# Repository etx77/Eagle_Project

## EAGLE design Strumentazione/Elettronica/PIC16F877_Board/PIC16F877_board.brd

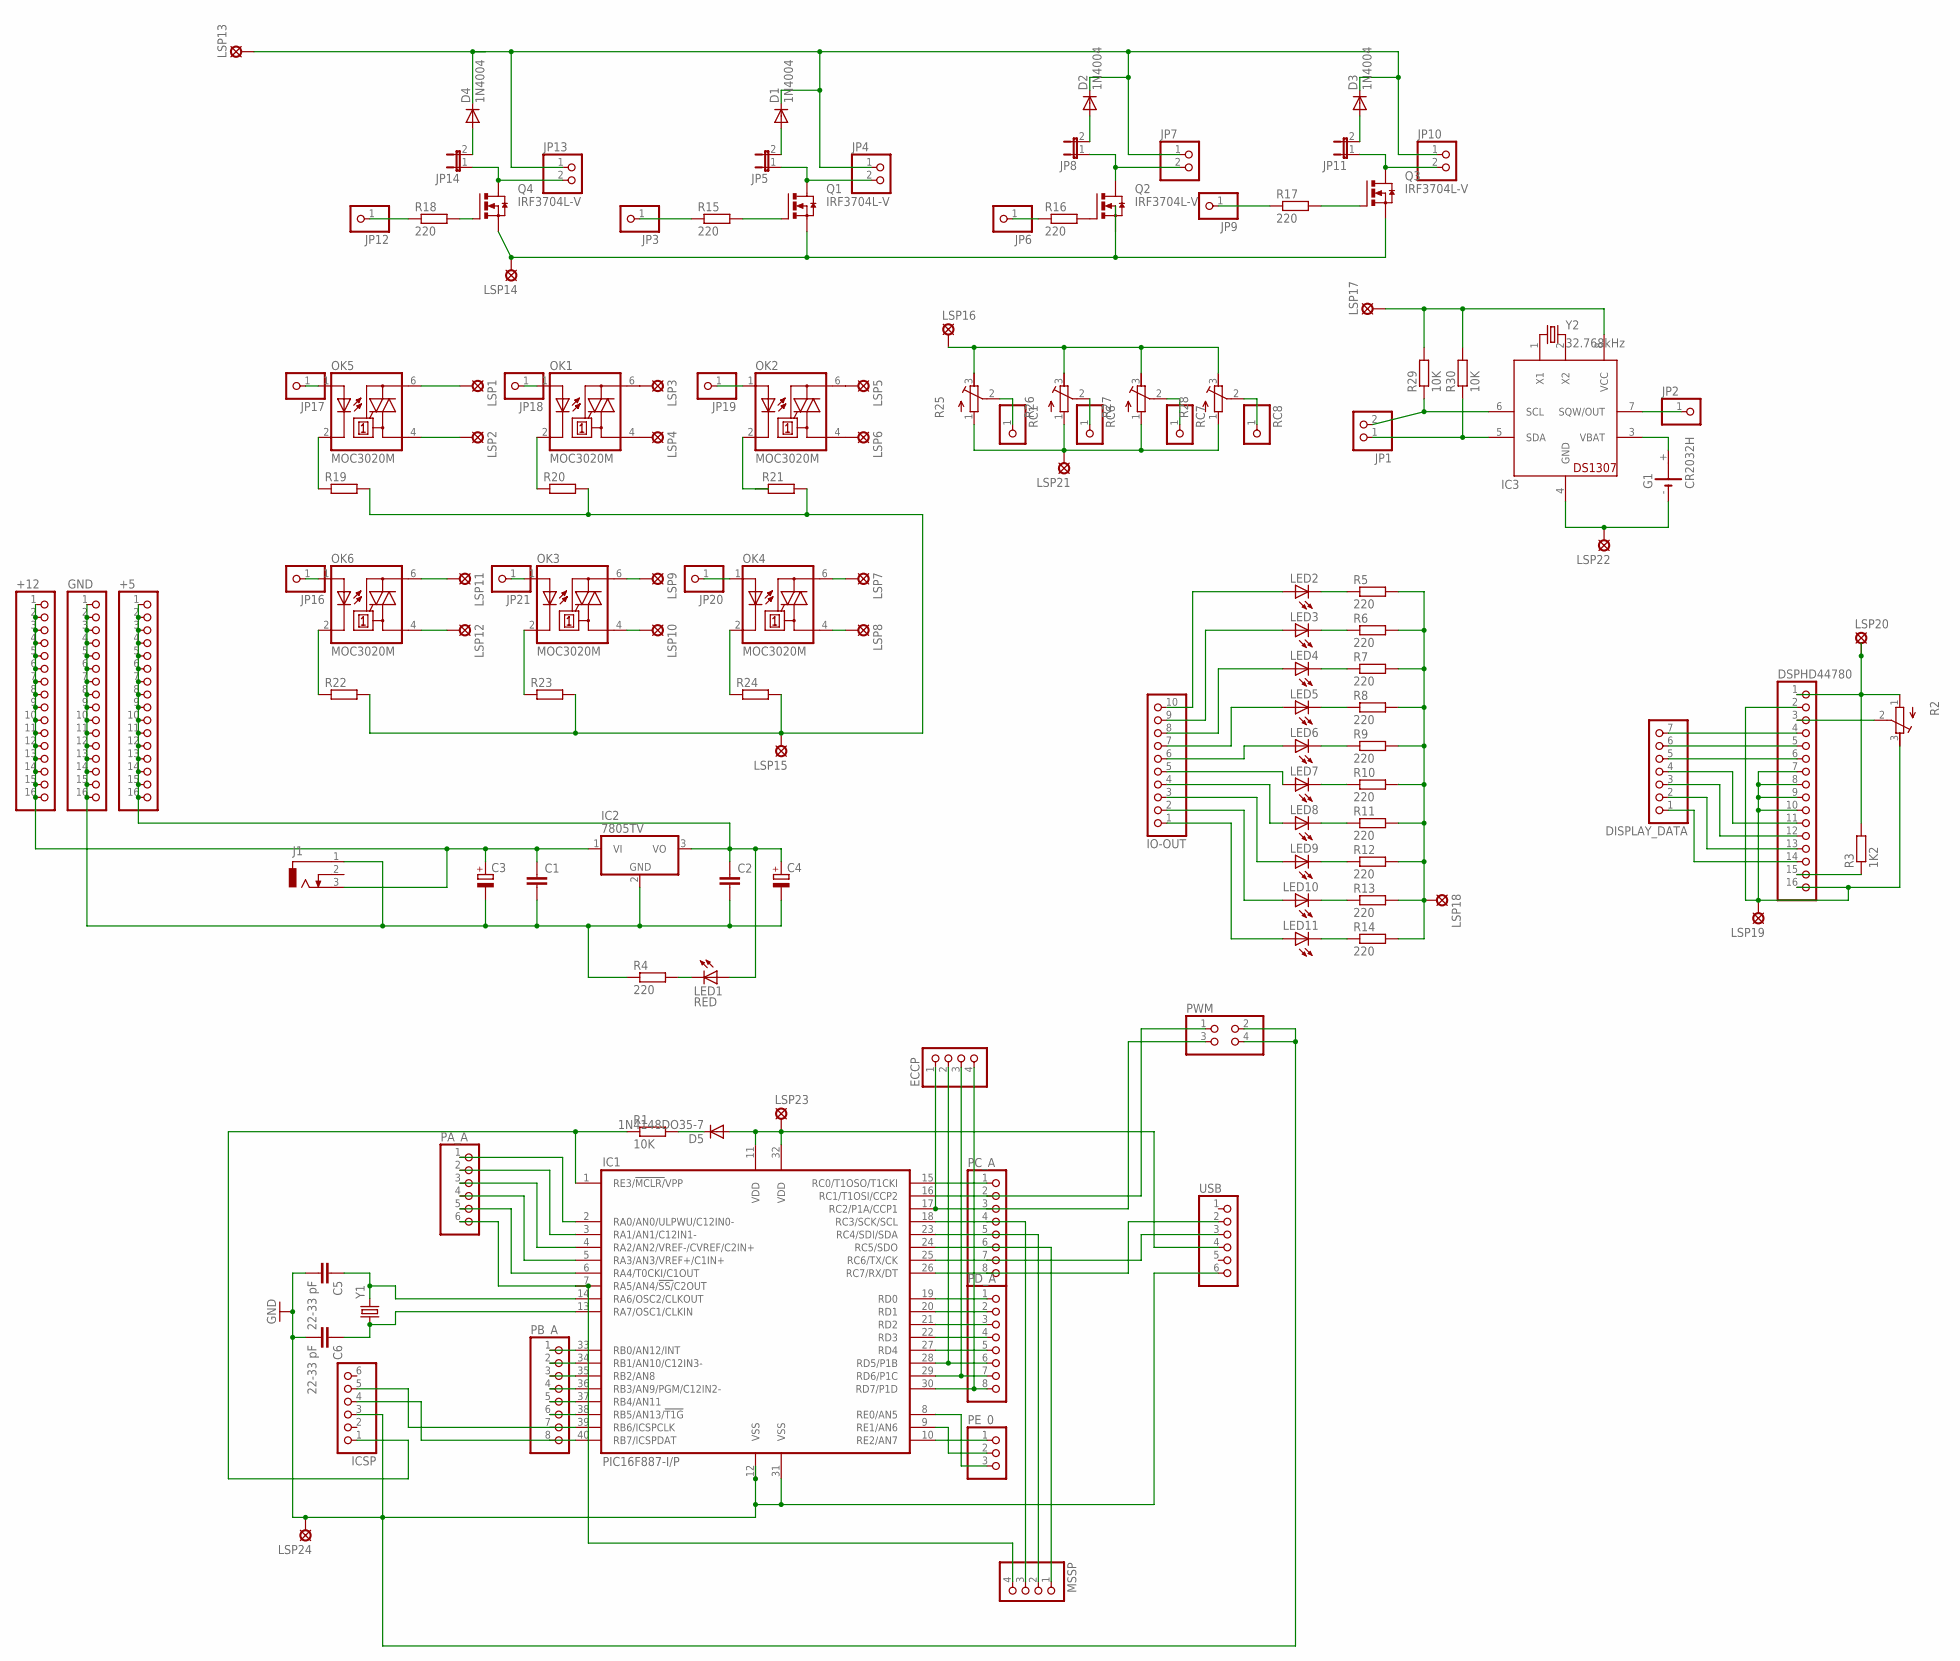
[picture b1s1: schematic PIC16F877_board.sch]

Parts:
+5, +12: PINHD-1X16; 1X16
C1, C2: C-EU050-025X075; C050-025X075
C3, C4: CPOL-EUE2,5-6E; E2,5-6E
C5, C6: 22-33 pF; C025-024X044
D1, D2, D3, D4: 1N4004; DO41-10
D5: 1N4148DO35-7; DO35-7
DISPLAY_DATA: PINHD-1X7; 1X07
DSPHD44780: PINHD-1X16; 1X16
ECCP: PINHD-1X4; 1X04
G1: CR2032H
GND: PINHD-1X16; 1X16
IC1: PIC16F887-I/P; DIL40
IC2: 7805TV; TO220V
IC3: DS1307; DIL08
ICSP: PINHD-1X6; 1X06
IO-OUT: PINHD-1X10; 1X10
J1: DCJ0303
JP1, JP4, JP7, JP10, JP13: PINHD-1X2; 1X02
JP2, JP3, JP6, JP9, JP12, JP16, JP17, JP18, JP19, JP20, JP21: PINHD-1X1; 1X01
JP5, JP8, JP11, JP14: JP1E; JP1
LED1: RED; LED5MM
LED2, LED3, LED4, LED5, LED6, LED7, LED8, LED9, LED10, LED11: LED3MM
LSP1, LSP2, LSP3, LSP4, LSP5, LSP6, LSP7, LSP8, LSP9, LSP10, LSP11, LSP12, LSP13, LSP14, LSP15, LSP16, LSP17, LSP18, LSP19, LSP20, LSP21, LSP22, LSP23, LSP24: LSP10
MSSP: PINHD-1X4; 1X04
OK1, OK2, OK3, OK4, OK5, OK6: MOC3020M; DIL06
PA_A: PINHD-1X6; 1X06
PB_A: PINHD-1X8; 1X08
PC_A: PINHD-1X8; 1X08
PD_A: PINHD-1X8; 1X08
PE_0: PINHD-1X3; 1X03
PWM: PINHD-2X2; 2X02
Q1, Q2, Q3, Q4: IRF3704L-V; TO262-V
R1, R29, R30: 10K; 0207/10
R2, R25, R26, R27, R28: R-TRIMM3339P; RTRIM3339P
R3: 1K2; 0207/10
R4, R5, R6, R7, R8, R9, R10, R11, R12, R13, R14, R15, R16, R17, R18: 220; 0207/10
R19, R20, R21, R22, R23, R24: R-EU_0207/10; 0207/10
RC1, RC6, RC7, RC8: PINHD-1X1; 1X01
USB: PINHD-1X6; 1X06
Y1: CRYSTALHC49UV; HC49U-V
Y2: 32.768kHz; TC26V

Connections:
GND: C5.2, C6.2, IC1.12 (VSS), IC1.31 (VSS), ICSP.3, LSP24.MP, PWM.2, PWM.4, USB.6
unnamed: C5.1, IC1.14 (RA6/OSC2/CLKOUT), Y1.2
unnamed: LED1.K (C), R4.2
unnamed: IC1.15 (RC0/T1OSO/T1CKI), PC_A.1
unnamed: IC1.33 (RB0/AN12/INT), PB_A.1
unnamed: IC1.34 (RB1/AN10/C12IN3-), PB_A.2
unnamed: IC1.35 (RB2/AN8), PB_A.3
unnamed: IC1.36 (RB3/AN9/PGM/C12IN2-), PB_A.4
unnamed: IC1.2 (RA0/AN0/ULPWU/C12IN0-), PA_A.1
unnamed: IC1.3 (RA1/AN1/C12IN1-), PA_A.2
unnamed: IC1.4 (RA2/AN2/VREF-/CVREF/C2IN+), PA_A.3
unnamed: IC1.5 (RA3/AN3/VREF+/C1IN+), PA_A.4
unnamed: IC1.6 (RA4/T0CKI/C1OUT), PA_A.5
unnamed: IC1.7 (RA5/AN4/!SS/!C2OUT), MSSP.4, PA_A.6
unnamed: DISPLAY_DATA.5, DSPHD44780.6
unnamed: IC1.1 (RE3/!MCLR/!VPP), ICSP.1, R1.1
unnamed: DISPLAY_DATA.6, DSPHD44780.5
unnamed: IC1.19 (RD0), PD_A.1
unnamed: IC1.37 (RB4/AN11), PB_A.5
unnamed: IC1.38 (RB5/AN13/!T1G), PB_A.6
unnamed: IC1.39 (RB6/ICSPCLK), ICSP.5, PB_A.7
unnamed: IC1.40 (RB7/ICSPDAT), ICSP.4, PB_A.8
unnamed: DSPHD44780.15, R3.1
unnamed: IC1.20 (RD1), PD_A.2
unnamed: IC1.16 (RC1/T1OSI/CCP2), PC_A.2, PWM.1
unnamed: C6.1, IC1.13 (RA7/OSC1/CLKIN), Y1.1
unnamed: C1.2, C2.2, C3.-, C4.-, GND.1, GND.2, GND.3, GND.4, GND.5, GND.6, GND.7, GND.8, GND.9, GND.10, GND.11, GND.12, GND.13, GND.14, GND.15, GND.16, IC2.2 (GND), J1.1, R4.1
unnamed: IC1.18 (RC3/SCK/SCL), MSSP.3, PC_A.4
unnamed: IC1.23 (RC4/SDI/SDA), MSSP.2, PC_A.5
unnamed: IC1.24 (RC5/SDO), MSSP.1, PC_A.6
unnamed: IC1.25 (RC6/TX/CK), PC_A.7, USB.3
unnamed: IC1.26 (RC7/RX/DT), PC_A.8, USB.2
unnamed: IC1.21 (RD2), PD_A.3
unnamed: IC1.22 (RD3), PD_A.4
unnamed: IC1.27 (RD4), PD_A.5
unnamed: ECCP.2, IC1.28 (RD5/P1B), PD_A.6
unnamed: ECCP.3, IC1.29 (RD6/P1C), PD_A.7
unnamed: ECCP.4, IC1.30 (RD7/P1D), PD_A.8
unnamed: ECCP.1, IC1.17 (RC2/P1A/CCP1), PC_A.3, PWM.3
unnamed: JP17.1, OK5.1 (A)
unnamed: Q1.1 (G), R15.2
unnamed: LED2.K (C), R5.1
unnamed: LED3.K (C), R6.1
unnamed: LED4.K (C), R7.1
unnamed: LED5.K (C), R8.1
unnamed: LED6.K (C), R9.1
unnamed: LED7.K (C), R10.1
unnamed: LED8.K (C), R11.1
unnamed: LED9.K (C), R12.1
unnamed: LED10.K (C), R13.1
unnamed: LED11.K (C), R14.1
unnamed: JP3.1, R15.1
unnamed: IO-OUT.10, LED2.A
unnamed: IO-OUT.9, LED3.A
unnamed: IO-OUT.8, LED4.A
unnamed: IO-OUT.7, LED5.A
unnamed: IO-OUT.6, LED6.A
unnamed: IO-OUT.5, LED7.A
unnamed: IO-OUT.4, LED8.A
unnamed: IO-OUT.3, LED9.A
unnamed: IO-OUT.2, LED10.A
unnamed: IO-OUT.1, LED11.A
unnamed: JP4.2, JP5.1, Q1.2 (D)
unnamed: JP18.1, OK1.1 (A)
unnamed: JP19.1, OK2.1 (A)
unnamed: D1.A, JP5.2
unnamed: JP20.1, OK4.1 (A)
unnamed: Q2.1 (G), R16.2
unnamed: JP6.1, R16.1
unnamed: JP7.2, JP8.1, Q2.2 (D)
unnamed: D2.A, JP8.2
unnamed: Q3.1 (G), R17.2
unnamed: JP9.1, R17.1
unnamed: JP10.2, JP11.1, Q3.2 (D)
unnamed: D3.A, JP11.2
unnamed: Q4.1 (G), R18.2
unnamed: JP12.1, R18.1
unnamed: JP13.2, JP14.1, Q4.2 (D)
unnamed: D4.A, JP14.2
unnamed: LSP1.MP, OK5.6 (A2)
unnamed: LSP2.MP, OK5.4 (A1)
unnamed: LSP3.MP, OK1.6 (A2)
unnamed: LSP4.MP, OK1.4 (A1)
unnamed: LSP5.MP, OK2.6 (A2)
unnamed: LSP6.MP, OK2.4 (A1)
unnamed: LSP7.MP, OK4.6 (A2)
unnamed: LSP8.MP, OK4.4 (A1)
unnamed: LSP9.MP, OK3.6 (A2)
unnamed: LSP10.MP, OK3.4 (A1)
unnamed: LSP11.MP, OK6.6 (A2)
unnamed: LSP12.MP, OK6.4 (A1)
unnamed: JP21.1, OK3.1 (A)
unnamed: OK2.2 (C), R21.1
unnamed: OK1.2 (C), R20.1
unnamed: OK5.2 (C), R19.1
unnamed: JP16.1, OK6.1 (A)
unnamed: OK3.2 (C), R23.1
unnamed: OK4.2 (C), R24.1
unnamed: OK6.2 (C), R22.1
unnamed: DISPLAY_DATA.1, DSPHD44780.14
unnamed: R25.2 (S), RC1.1
unnamed: R26.2 (S), RC6.1
unnamed: R27.2 (S), RC7.1
unnamed: R28.2 (S), RC8.1
unnamed: DISPLAY_DATA.2, DSPHD44780.13
unnamed: DISPLAY_DATA.3, DSPHD44780.12
unnamed: DISPLAY_DATA.4, DSPHD44780.11
unnamed: DISPLAY_DATA.7, DSPHD44780.4
unnamed: IC1.9 (RE1/AN6), PE_0.2
unnamed: DSPHD44780.3, R2.2 (S)
unnamed: IC1.8 (RE0/AN5), PE_0.3
unnamed: IC1.10 (RE2/AN7), PE_0.1
unnamed: D5.C, R1.2
unnamed: IC3.6 (SCL), JP1.2, R29.1
unnamed: IC3.5 (SDA), JP1.1, R30.1
unnamed: IC3.8 (VCC), LSP17.MP, R29.2, R30.2
unnamed: IC3.7 (SQW/OUT), JP2.1
unnamed: G1.+, IC3.3 (VBAT)
unnamed: D1.C, D2.C, D3.C, D4.C, JP4.1, JP7.1, JP10.1, JP13.1, LSP13.MP
unnamed: LSP14.MP, Q1.3 (S), Q2.3 (S), Q3.3 (S), Q4.3 (S)
unnamed: IC3.1 (X1), Y2.1
unnamed: IC3.2 (X2), Y2.2
unnamed: LSP15.MP, R19.2, R20.2, R21.2, R22.2, R23.2, R24.2
unnamed: LSP18.MP, R5.2, R6.2, R7.2, R8.2, R9.2, R10.2, R11.2, R12.2, R13.2, R14.2
unnamed: LSP16.MP, R25.3 (E), R26.3 (E), R27.3 (E), R28.3 (E)
unnamed: DSPHD44780.1, LSP20.MP, R2.1 (A), R3.2
unnamed: DSPHD44780.2, DSPHD44780.7, DSPHD44780.8, DSPHD44780.9, DSPHD44780.10, DSPHD44780.16, LSP19.MP, R2.3 (E)
unnamed: G1.-, IC3.4 (GND), LSP22.MP
unnamed: LSP21.MP, R25.1 (A), R26.1 (A), R27.1 (A), R28.1 (A)
unnamed: +12.1, +12.2, +12.3, +12.4, +12.5, +12.6, +12.7, +12.8, +12.9, +12.10, +12.11, +12.12, +12.13, +12.14, +12.15, +12.16, C1.1, C3.+, IC2.1 (VI), J1.3
unnamed: D5.A, IC1.11 (VDD), IC1.32 (VDD), LSP23.MP, USB.4
unnamed: +5.1, +5.2, +5.3, +5.4, +5.5, +5.6, +5.7, +5.8, +5.9, +5.10, +5.11, +5.12, +5.13, +5.14, +5.15, +5.16, C2.1, C4.+, IC2.3 (VO), LED1.A

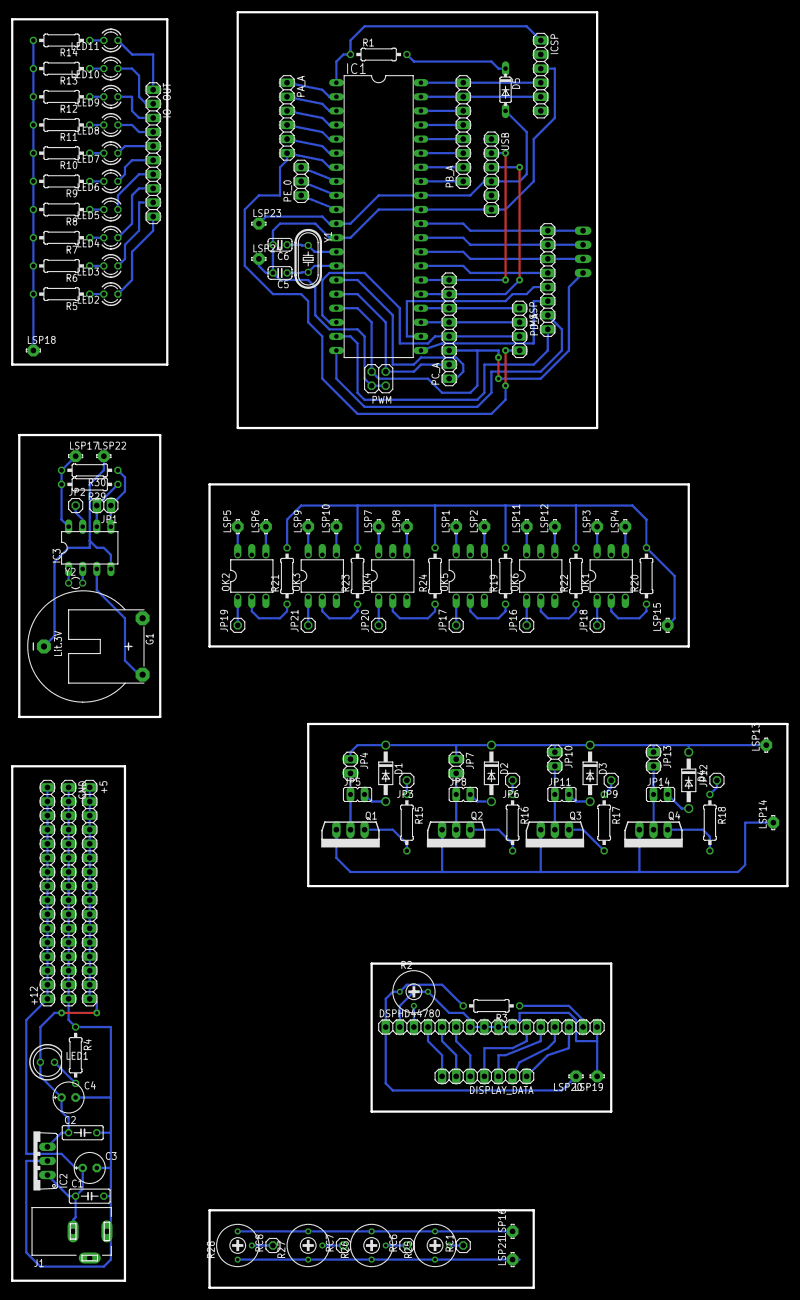
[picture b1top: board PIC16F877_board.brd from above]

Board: 2 copper layers, 139.7 x 229.9 mm, 133 parts (1 on the bottom side), 132 nets.

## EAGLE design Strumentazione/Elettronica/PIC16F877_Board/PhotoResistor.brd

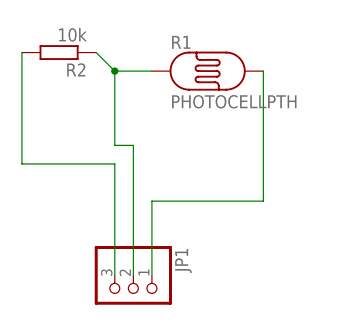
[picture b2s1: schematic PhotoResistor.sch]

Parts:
JP1: PINHD-1X3/90; 1X03/90
R1: PHOTOCELLPTH; PHOTOCELL
R2: 10k; 0207/7

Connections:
unnamed: JP1.2, R1.1, R2.1
unnamed: JP1.3, R2.2
unnamed: JP1.1, R1.2

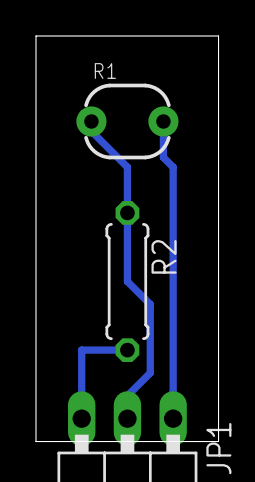
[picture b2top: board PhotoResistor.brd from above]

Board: 2 copper layers, 10.1 x 22.5 mm, 3 parts (0 on the bottom side), 3 nets.

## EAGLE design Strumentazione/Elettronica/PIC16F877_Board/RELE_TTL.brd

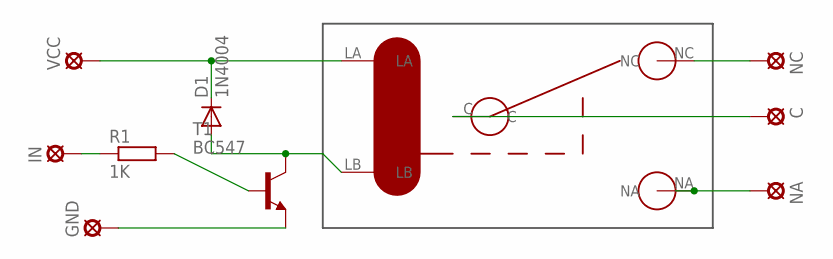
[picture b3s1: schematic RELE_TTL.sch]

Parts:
C: LSP10
D1: 1N4004; DO41-10
GND: LSP10
IN: LSP10
NA: LSP10
NC: LSP10
R1: 1K; 0207/2V
RL1: RELE; RELE_1
T1: BC547; TO92
VCC: LSP10

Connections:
unnamed: IN.MP, R1.1
unnamed: D1.C, RL1.LA, VCC.MP
unnamed: D1.A, RL1.LB, T1.3 (C)
unnamed: R1.2, T1.2 (B)
unnamed: GND.MP, T1.1 (E)
unnamed: NC.MP, RL1.NC
unnamed: C.MP, RL1.C
unnamed: NA.MP, RL1.NA

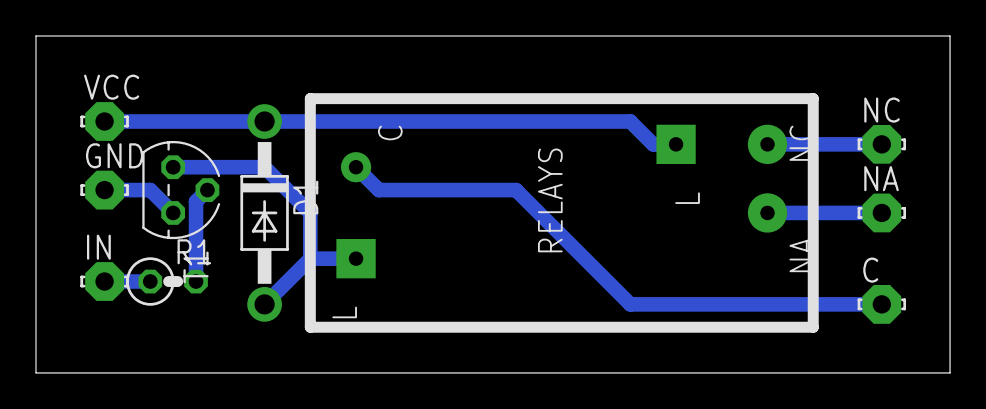
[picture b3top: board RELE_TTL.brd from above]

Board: 2 copper layers, 50.8 x 18.7 mm, 10 parts (0 on the bottom side), 8 nets.

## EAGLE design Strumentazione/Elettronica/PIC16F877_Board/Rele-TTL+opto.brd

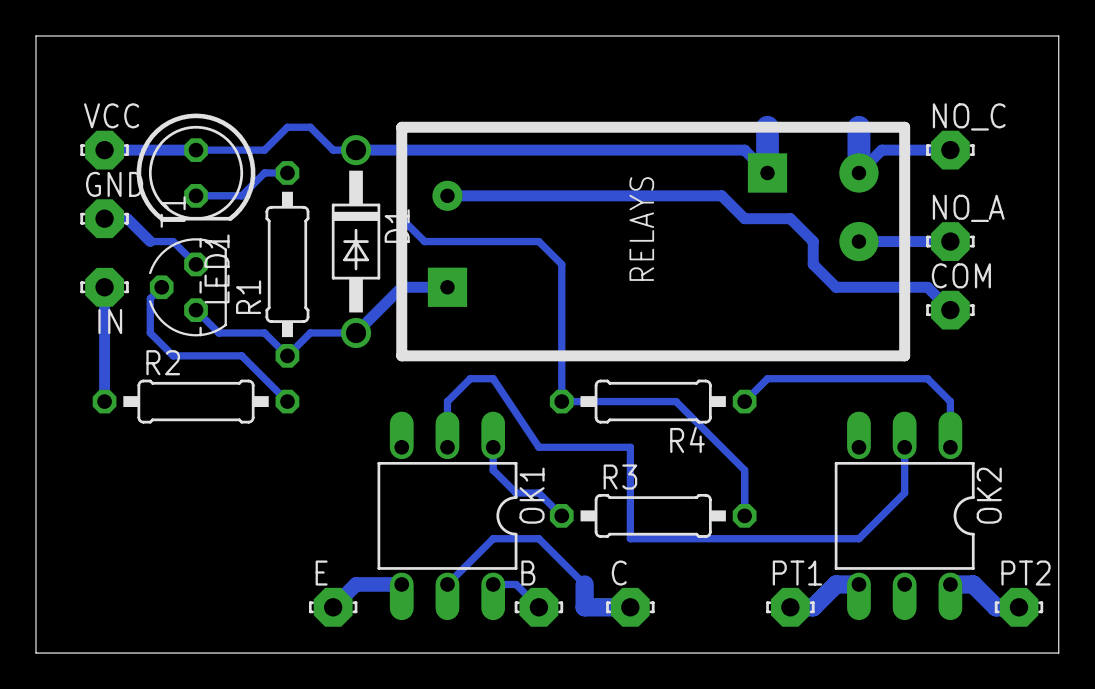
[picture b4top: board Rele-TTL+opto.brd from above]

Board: 2 copper layers, 56.8 x 34.3 mm, 21 parts (0 on the bottom side), 17 nets.

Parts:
B: LSP10
C: LSP10
COM: LSP10
D1: 1N4004; DO41-10
E: LSP10
GND: LSP10
IN: LSP10
LED1: red; LED5MM
NO_A: LSP10
NO_C: LSP10
OK1: 4N25M; DIL06
OK2: MOC3020M; DIL06
PT1, PT2: LSP10
R1, R3, R4: 220; 0207/10
R2: 4K7; 0207/10
RL1: RELE; RELE_1
T1: BC547; TO92
VCC: LSP10

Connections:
unnamed: LED1.K, R1.2
unnamed: COM.MP, RL1.C
unnamed: R2.2, T1.2
unnamed: D1.A, R1.1, RL1.LB, T1.3
unnamed: NO_A.MP, RL1.NA
unnamed: NO_C.MP, RL1.NC
unnamed: IN.MP, R2.1
unnamed: OK1.2, OK2.2
unnamed: D1.C, LED1.A, R3.2, R4.2, RL1.LA, VCC.MP
unnamed: OK2.1, R4.1
unnamed: GND.MP, T1.1
unnamed: OK1.1, R3.1
unnamed: E.MP, OK1.4
unnamed: C.MP, OK1.5
unnamed: OK2.4, PT1.MP
unnamed: OK2.6, PT2.MP
unnamed: B.MP, OK1.6

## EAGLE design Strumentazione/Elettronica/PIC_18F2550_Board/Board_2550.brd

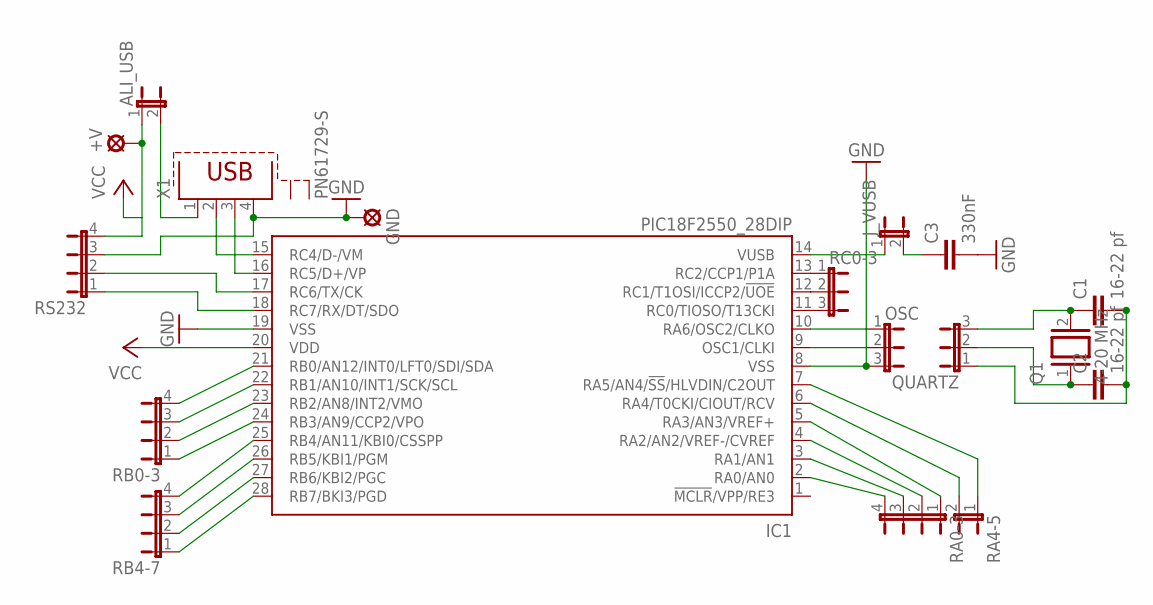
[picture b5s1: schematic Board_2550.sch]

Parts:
+V: SE14
ALI_USB: JP1E; JP1
C1, C2: 16-22 pf; C025-024X044
C3: 330nF; C025-024X044
GND: SE14
IC1: PIC18F2550_28DIP; DIL28-3
J_VUSB: JP1E; JP1
OSC: JP2E; JP2
Q1: 4-20 MHz; Q
QUARTZ: JP2W
RA0-3: JP4E; JP4
RA4-5: JP1E; JP1
RB0-3, RB4-7: JP4E; JP4
RC0-3: JP2E; JP2
RS232: JP4E; JP4
X1: PN61729-S

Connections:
GND: C3.2, GND.MP, IC1.8 (VSS), IC1.19 (VSS), OSC.3, RS232.3, X1.4
unnamed: IC1.10 (RA6/OSC2/CLKO), OSC.1
unnamed: IC1.9 (OSC1/CLKI), OSC.2
unnamed: IC1.15 (RC4/D-/VM), X1.2
unnamed: C1.1, Q1.2, QUARTZ.3
unnamed: C2.1, Q1.1, QUARTZ.2
unnamed: IC1.6 (RA4/T0CKI/CIOUT/RCV), RA4-5.2
unnamed: IC1.16 (RC5/D+/VP), X1.3
unnamed: IC1.5 (RA3/AN3/VREF+), RA0-3.1
unnamed: IC1.4 (RA2/AN2/VREF-/CVREF), RA0-3.2
unnamed: IC1.17 (RC6/TX/CK), RS232.2
unnamed: IC1.18 (RC7/RX/DT/SDO), RS232.1
unnamed: IC1.24 (RB3/AN9/CCP2/VPO), RB0-3.1
unnamed: IC1.23 (RB2/AN8/INT2/VMO), RB0-3.2
unnamed: IC1.22 (RB1/AN10/INT1/SCK/SCL), RB0-3.3
unnamed: IC1.21 (RB0/AN12/INT0/LFT0/SDI/SDA), RB0-3.4
unnamed: IC1.28 (RB7/BKI3/PGD), RB4-7.1
unnamed: IC1.27 (RB6/KBI2/PGC), RB4-7.2
unnamed: IC1.26 (RB5/KBI1/PGM), RB4-7.3
unnamed: IC1.25 (RB4/AN11/KBI0/CSSPP), RB4-7.4
unnamed: IC1.3 (RA1/AN1), RA0-3.3
unnamed: IC1.2 (RA0/AN0), RA0-3.4
unnamed: IC1.7 (RA5/AN4/!SS!/HLVDIN/C2OUT), RA4-5.1
unnamed: C1.2, C2.2, QUARTZ.1
unnamed: +V.MP, ALI_USB.1, IC1.20 (VDD), RS232.4
unnamed: IC1.13 (RC2/CCP1/P1A), RC0-3.1
unnamed: IC1.12 (RC1/T1OSI/ICCP2/!UOE), RC0-3.2
unnamed: IC1.11 (RC0/TIOSO/T13CKI), RC0-3.3
unnamed: C3.1, J_VUSB.2
unnamed: IC1.14 (VUSB), J_VUSB.1
unnamed: ALI_USB.2, X1.1

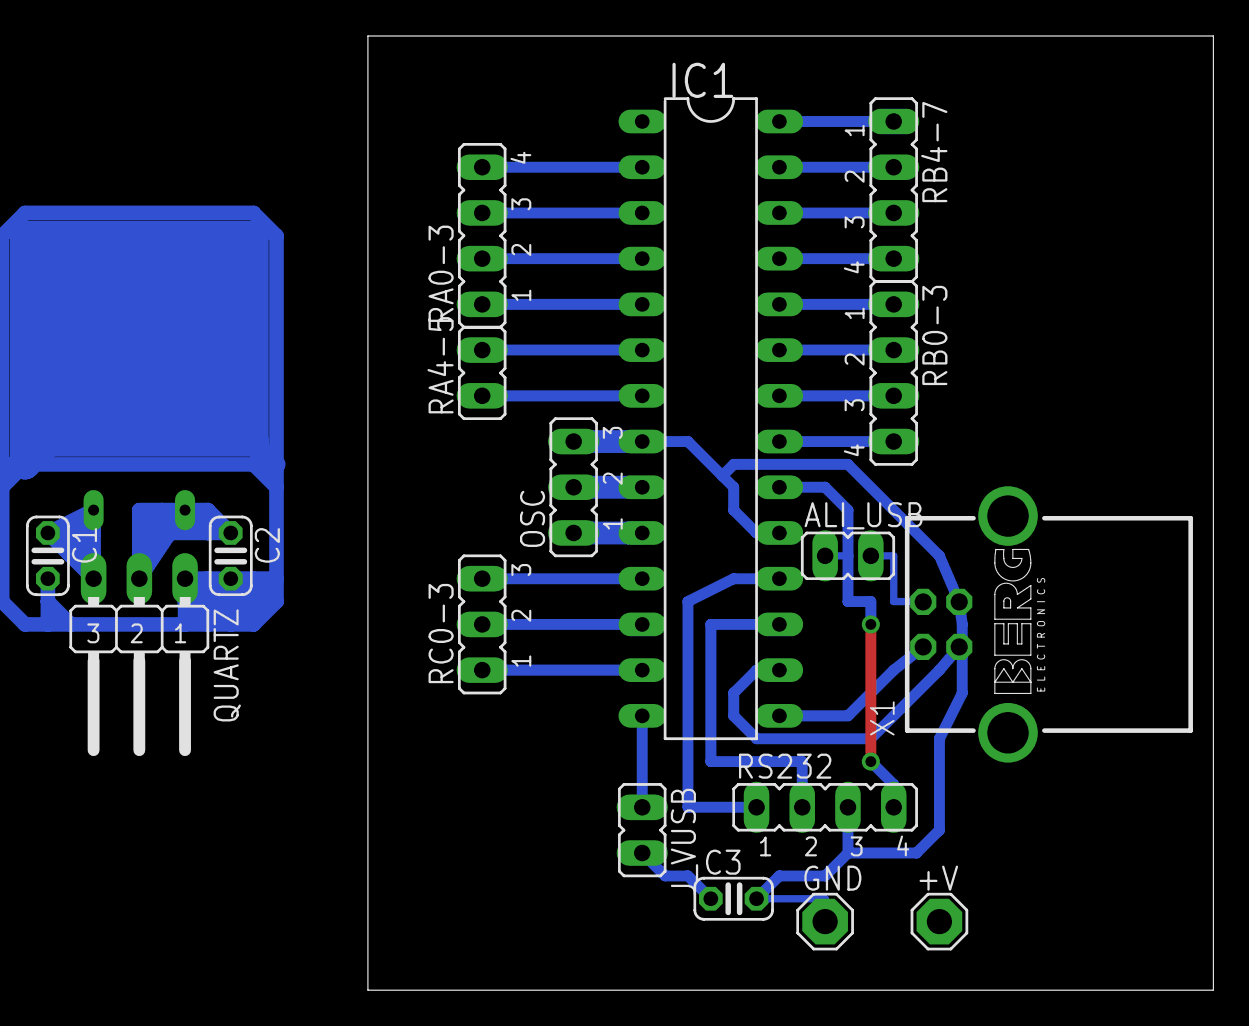
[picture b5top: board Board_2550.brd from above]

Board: 2 copper layers, 47.0 x 53.0 mm, 18 parts (1 on the bottom side), 31 nets.

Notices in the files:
parts and their libraries:
SparkFun-FreqCtrl: Licensing: Creative Commons ShareAlike 4.0 International - https://creativecommons.org/licenses/by-sa/4.0
